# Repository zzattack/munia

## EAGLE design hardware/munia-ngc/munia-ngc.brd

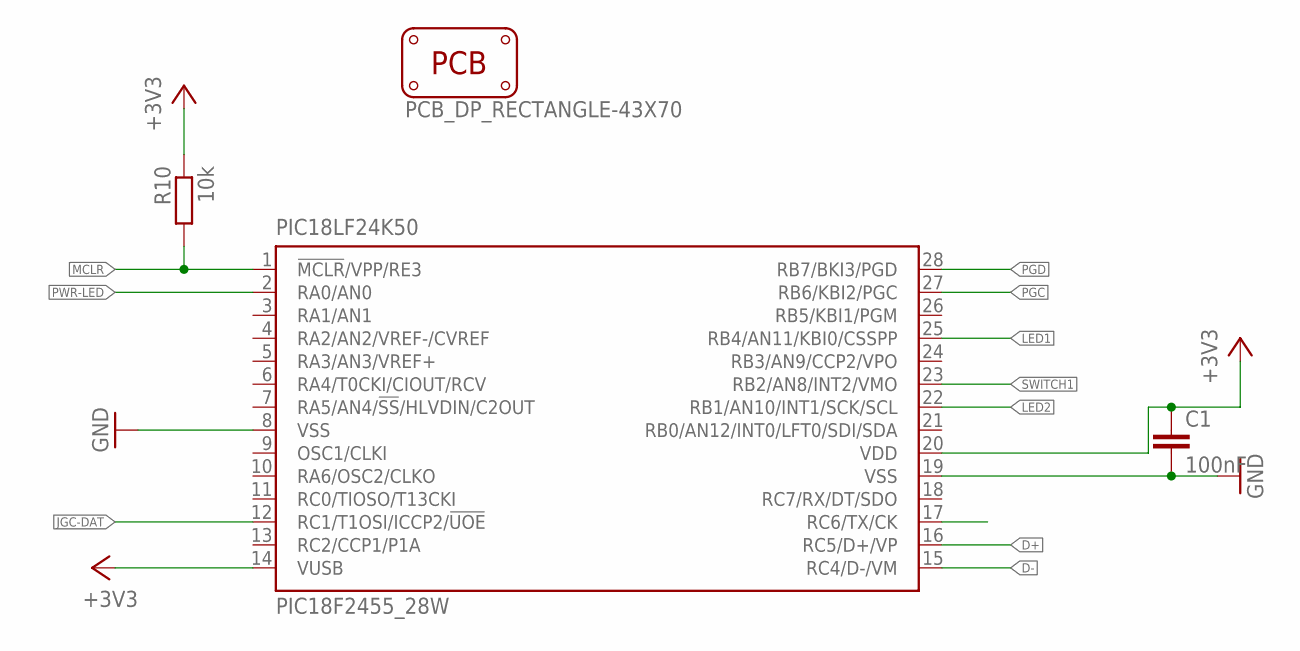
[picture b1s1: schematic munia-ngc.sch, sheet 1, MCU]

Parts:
C1: 100nF; C0603
PCB1: PCB_DP_RECTANGLE-43X70; DP7043_V1
PIC18LF24K50: PIC18F2455_28W; SO28W
R10: 10k; R0603

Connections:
+3V3: C1.1, PIC18LF24K50.14 (VUSB), PIC18LF24K50.20 (VDD), R10.1; also elsewhere on the board
D+: PIC18LF24K50.16 (RC5/D+/VP); also elsewhere on the board
D-: PIC18LF24K50.15 (RC4/D-/VM); also elsewhere on the board
GND: C1.2, PIC18LF24K50.8 (VSS), PIC18LF24K50.19 (VSS); also elsewhere on the board
JGC-DAT: PIC18LF24K50.12 (RC1/T1OSI/ICCP2/!UOE); also elsewhere on the board
LED1: PIC18LF24K50.25 (RB4/AN11/KBI0/CSSPP); also elsewhere on the board
LED2: PIC18LF24K50.22 (RB1/AN10/INT1/SCK/SCL); also elsewhere on the board
MCLR: PIC18LF24K50.1 (!MCLR!/VPP/RE3), R10.2; also elsewhere on the board
PGC: PIC18LF24K50.27 (RB6/KBI2/PGC); also elsewhere on the board
PGD: PIC18LF24K50.28 (RB7/BKI3/PGD); also elsewhere on the board
PWR-LED: PIC18LF24K50.2 (RA0/AN0); also elsewhere on the board
SWITCH1: PIC18LF24K50.23 (RB2/AN8/INT2/VMO); also elsewhere on the board

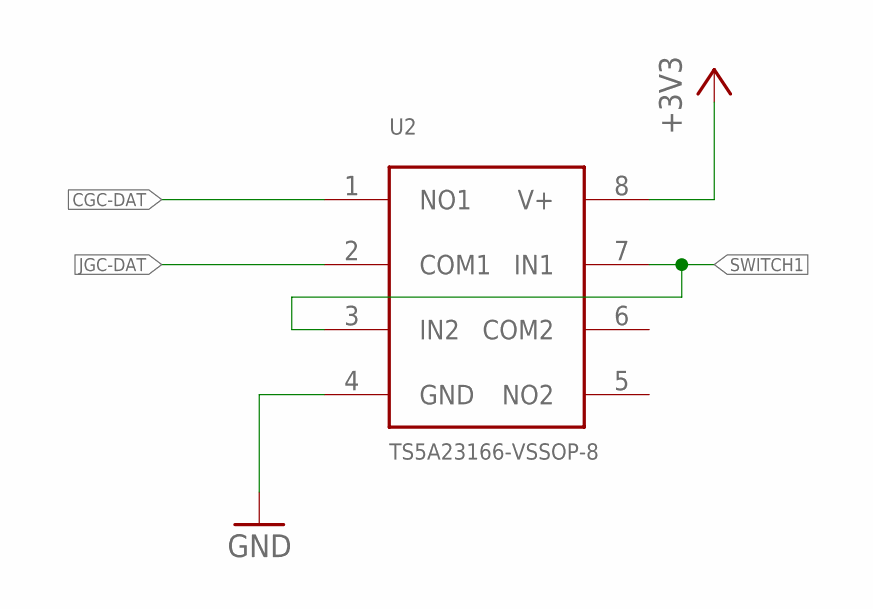
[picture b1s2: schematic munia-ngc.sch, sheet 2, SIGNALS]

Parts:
U2: TS5A23166-VSSOP-8; SOT765

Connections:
+3V3: U2.8 (V+); also elsewhere on the board
CGC-DAT: U2.1 (NO1); also elsewhere on the board
GND: U2.4 (GND); also elsewhere on the board
JGC-DAT: U2.2 (COM1); also elsewhere on the board
SWITCH1: U2.3 (IN2), U2.7 (IN1); also elsewhere on the board

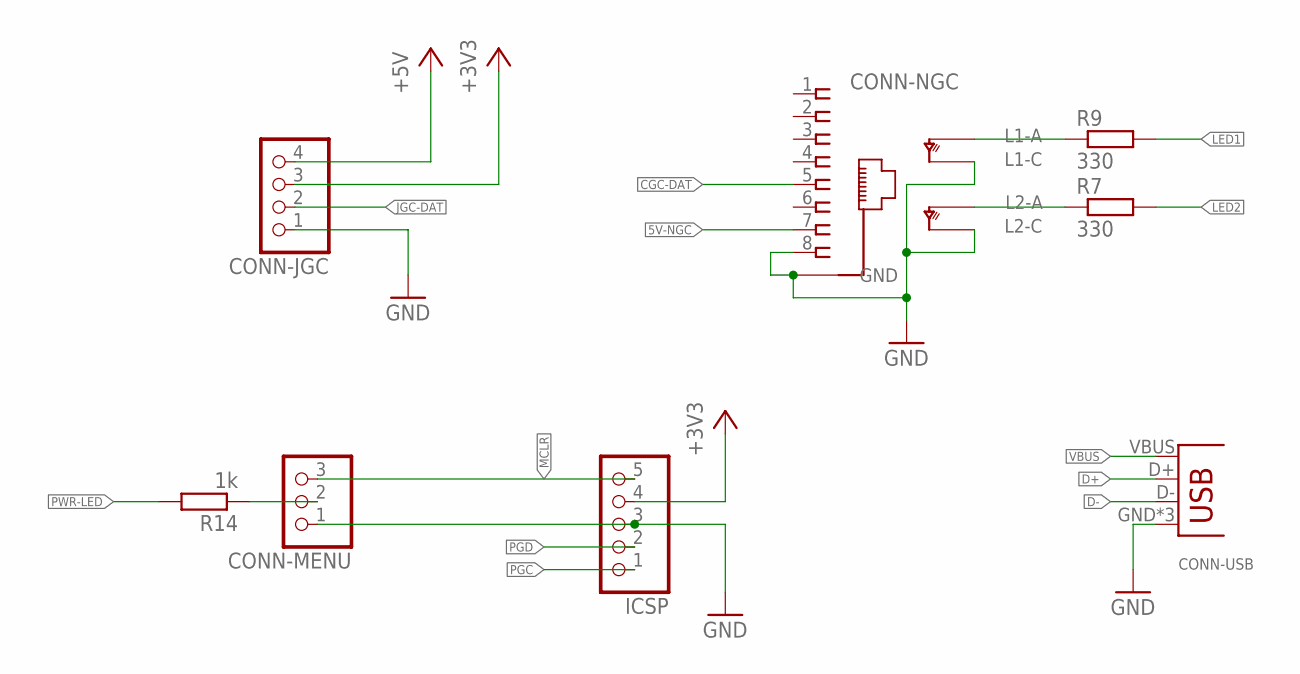
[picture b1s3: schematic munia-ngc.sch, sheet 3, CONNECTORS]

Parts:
CONN-JGC: PINHD-1X4; 1X04
CONN-MENU: PINHD-1X3; 1X03
CONN-NGC: RJ45-NIELS
CONN-USB: USB-B-NIELS; USB-B-H
ICSP: PINHD-1X5; 1X05
R7, R9: 330; R0603
R14: 1k; R0603

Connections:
5V-NGC: CONN-NGC.7; also elsewhere on the board
+3V3: CONN-JGC.3, ICSP.4; also elsewhere on the board
+5V: CONN-JGC.4; also elsewhere on the board
CGC-DAT: CONN-NGC.5; also elsewhere on the board
D+: CONN-USB.D+; also elsewhere on the board
D-: CONN-USB.D-; also elsewhere on the board
GND: CONN-JGC.1, CONN-MENU.1, CONN-NGC.8, CONN-NGC.GND@5 (GND), CONN-NGC.GND@6 (GND), CONN-NGC.LED-GREEN-C (L2C), CONN-NGC.LED-ORANGE-C (L1C), CONN-USB.GND, CONN-USB.GND@1 (GND), CONN-USB.GND@2 (GND), ICSP.3; also elsewhere on the board
JGC-DAT: CONN-JGC.2; also elsewhere on the board
LED1: R9.2; also elsewhere on the board
LED2: R7.2; also elsewhere on the board
MCLR: CONN-MENU.3, ICSP.5; also elsewhere on the board
unnamed: CONN-MENU.2, R14.1
unnamed: CONN-NGC.LED-ORANGE-A (L1A), R9.1
unnamed: CONN-NGC.LED-GREEN-A (L2A), R7.1
PGC: ICSP.1; also elsewhere on the board
PGD: ICSP.2; also elsewhere on the board
PWR-LED: R14.2; also elsewhere on the board
VBUS: CONN-USB.VBUS; also elsewhere on the board

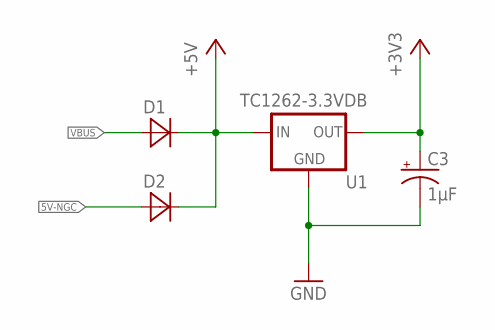
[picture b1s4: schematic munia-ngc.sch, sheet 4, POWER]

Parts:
C3: 1µF; EIA3216
D1, D2: MBR120VLSFT1G; SOD123
U1: TC1262-3.3VDB; SOT230P700X180-4N

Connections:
5V-NGC: D2.2 (A); also elsewhere on the board
+3V3: C3.A (+), U1.3 (OUT); also elsewhere on the board
+5V: D1.1 (C), D2.1 (C), U1.1 (IN); also elsewhere on the board
GND: C3.C (-), U1.2 (GND), U1.4 (GND); also elsewhere on the board
VBUS: D1.2 (A); also elsewhere on the board

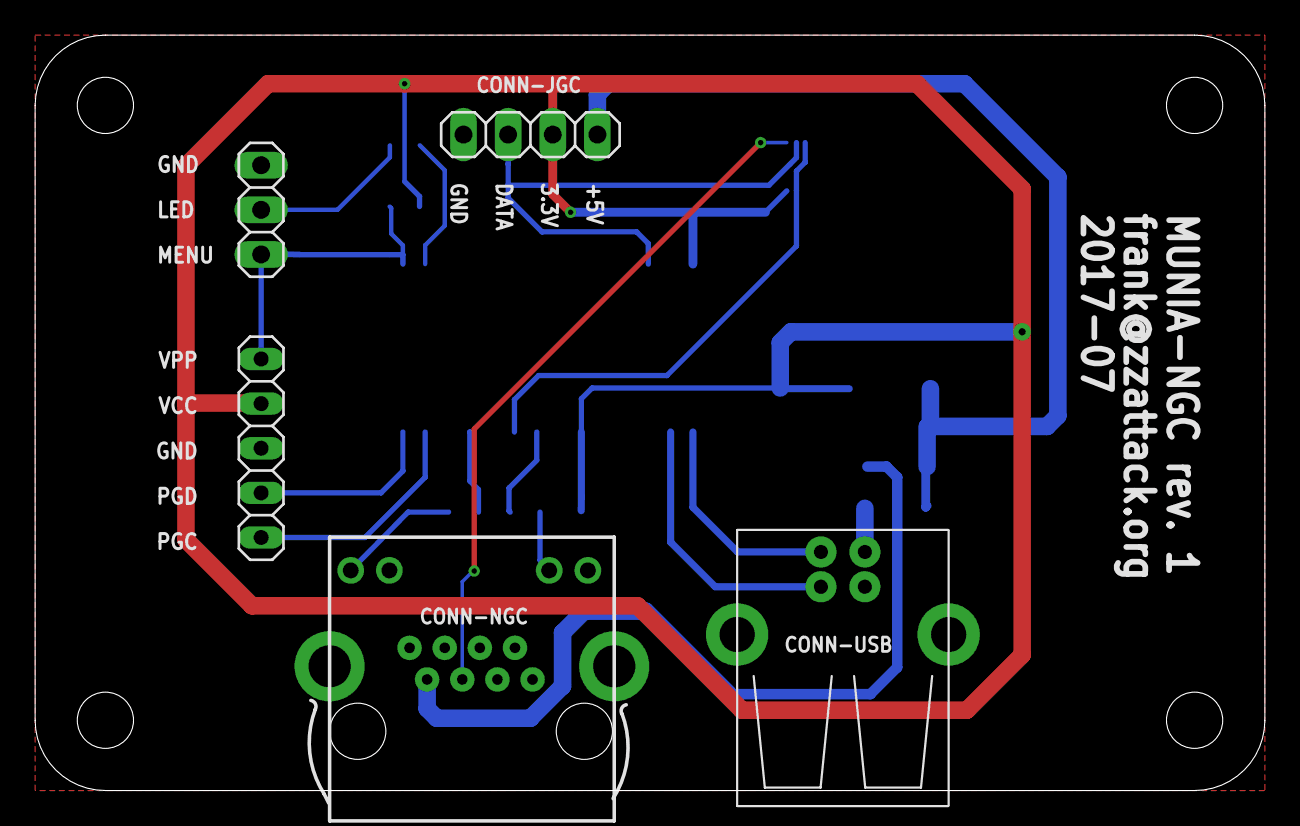
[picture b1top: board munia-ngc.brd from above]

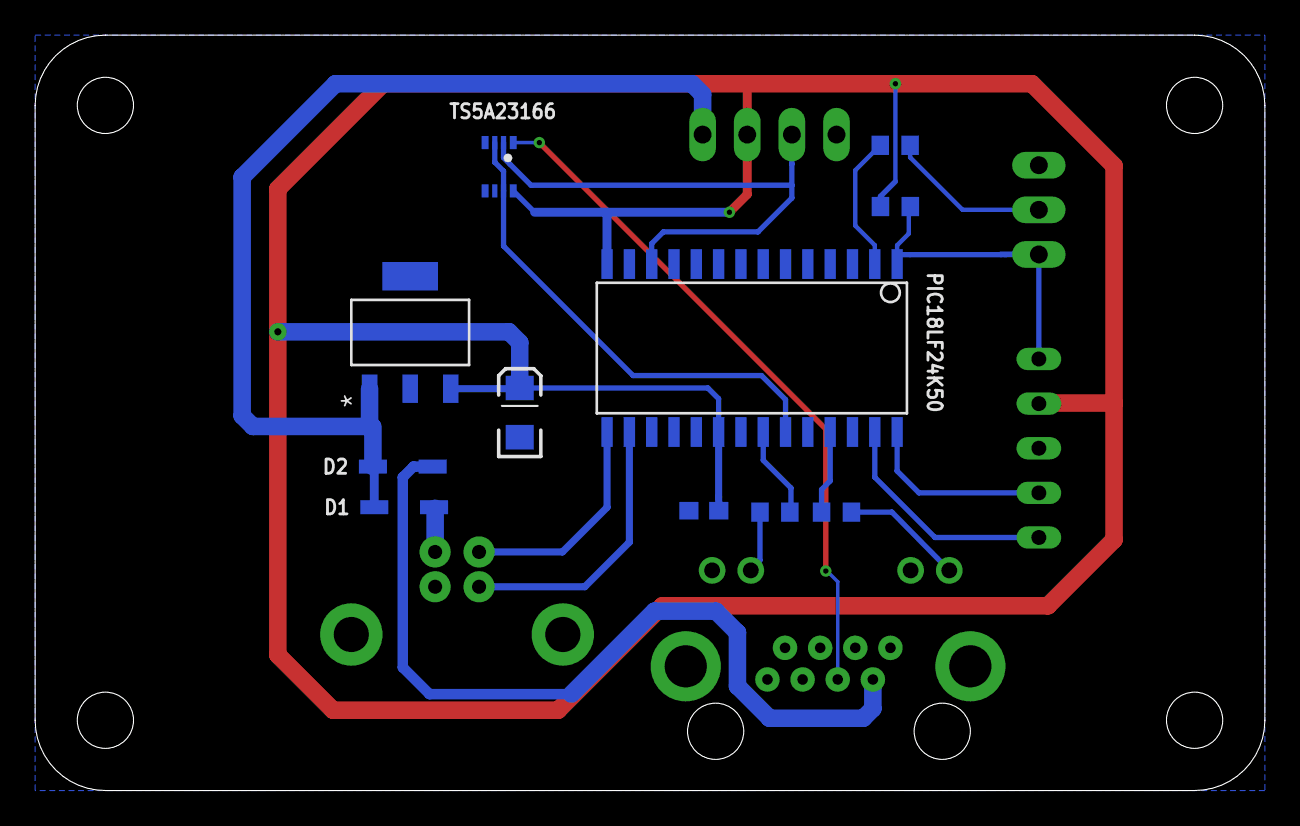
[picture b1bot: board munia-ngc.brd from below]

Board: 2 copper layers, 70.0 x 43.0 mm, 17 parts (11 on the bottom side), 19 nets.

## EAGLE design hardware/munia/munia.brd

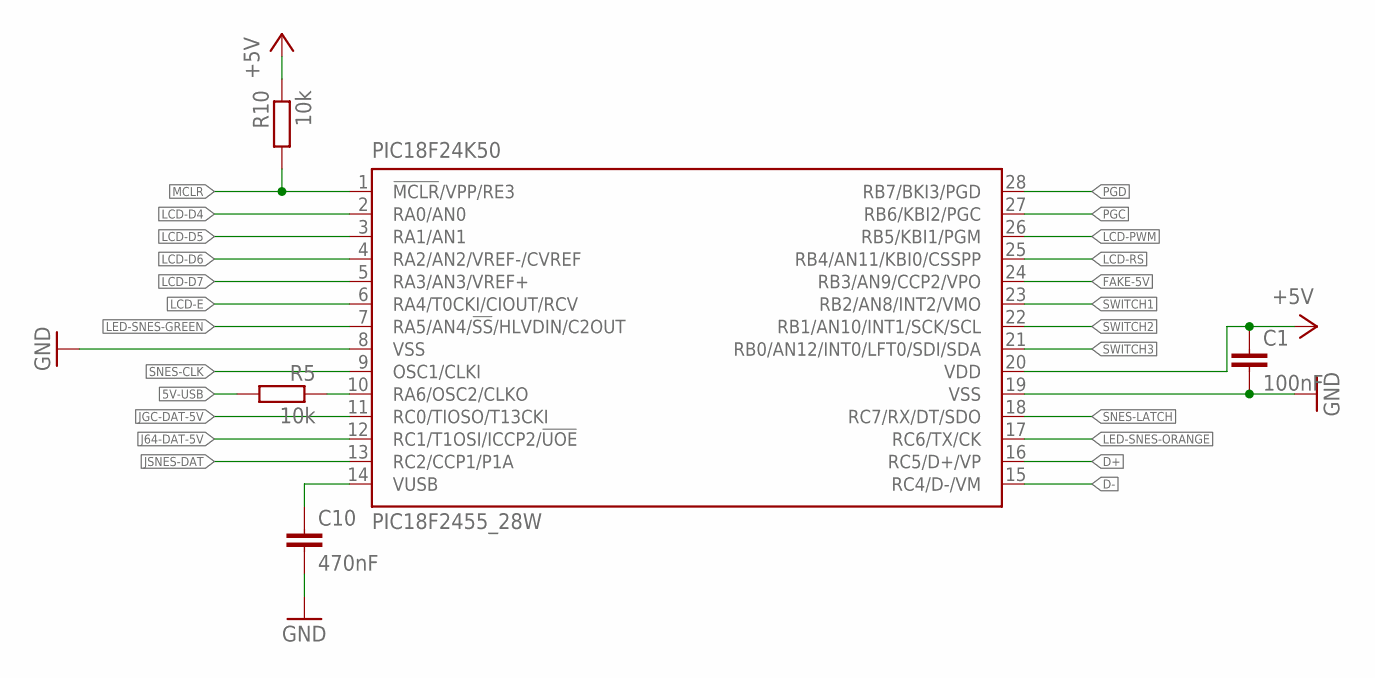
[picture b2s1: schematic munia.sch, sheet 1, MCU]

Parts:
C1: 100nF; C0603
C10: 470nF; C0603
PIC18F24K50: PIC18F2455_28W; SO28W
R5, R10: 10k; R0603

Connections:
5V-USB: R5.2; also elsewhere on the board
+5V: C1.1, PIC18F24K50.20 (VDD), R10.1; also elsewhere on the board
D+: PIC18F24K50.16 (RC5/D+/VP); also elsewhere on the board
D-: PIC18F24K50.15 (RC4/D-/VM); also elsewhere on the board
FAKE-5V: PIC18F24K50.24 (RB3/AN9/CCP2/VPO); also elsewhere on the board
J64-DAT-5V: PIC18F24K50.12 (RC1/T1OSI/ICCP2/!UOE); also elsewhere on the board
JGC-DAT-5V: PIC18F24K50.11 (RC0/TIOSO/T13CKI); also elsewhere on the board
JSNES-DAT: PIC18F24K50.13 (RC2/CCP1/P1A); also elsewhere on the board
LCD-D4: PIC18F24K50.2 (RA0/AN0); also elsewhere on the board
LCD-D5: PIC18F24K50.3 (RA1/AN1); also elsewhere on the board
LCD-D6: PIC18F24K50.4 (RA2/AN2/VREF-/CVREF); also elsewhere on the board
LCD-D7: PIC18F24K50.5 (RA3/AN3/VREF+); also elsewhere on the board
LCD-E: PIC18F24K50.6 (RA4/T0CKI/CIOUT/RCV); also elsewhere on the board
LCD-PWM: PIC18F24K50.26 (RB5/KBI1/PGM); also elsewhere on the board
LCD-RS: PIC18F24K50.25 (RB4/AN11/KBI0/CSSPP); also elsewhere on the board
LED-SNES-GREEN: PIC18F24K50.7 (RA5/AN4/!SS!/HLVDIN/C2OUT); also elsewhere on the board
LED-SNES-ORANGE: PIC18F24K50.17 (RC6/TX/CK); also elsewhere on the board
MCLR: PIC18F24K50.1 (!MCLR!/VPP/RE3), R10.2; also elsewhere on the board
unnamed: C10.1, PIC18F24K50.14 (VUSB)
SNES-CLK: PIC18F24K50.9 (OSC1/CLKI); also elsewhere on the board
SNES-LATCH: PIC18F24K50.18 (RC7/RX/DT/SDO); also elsewhere on the board
SWITCH1: PIC18F24K50.23 (RB2/AN8/INT2/VMO); also elsewhere on the board
SWITCH2: PIC18F24K50.22 (RB1/AN10/INT1/SCK/SCL); also elsewhere on the board
SWITCH3: PIC18F24K50.21 (RB0/AN12/INT0/LFT0/SDI/SDA); also elsewhere on the board
USB-SENSE: PIC18F24K50.10 (RA6/OSC2/CLKO), R5.1

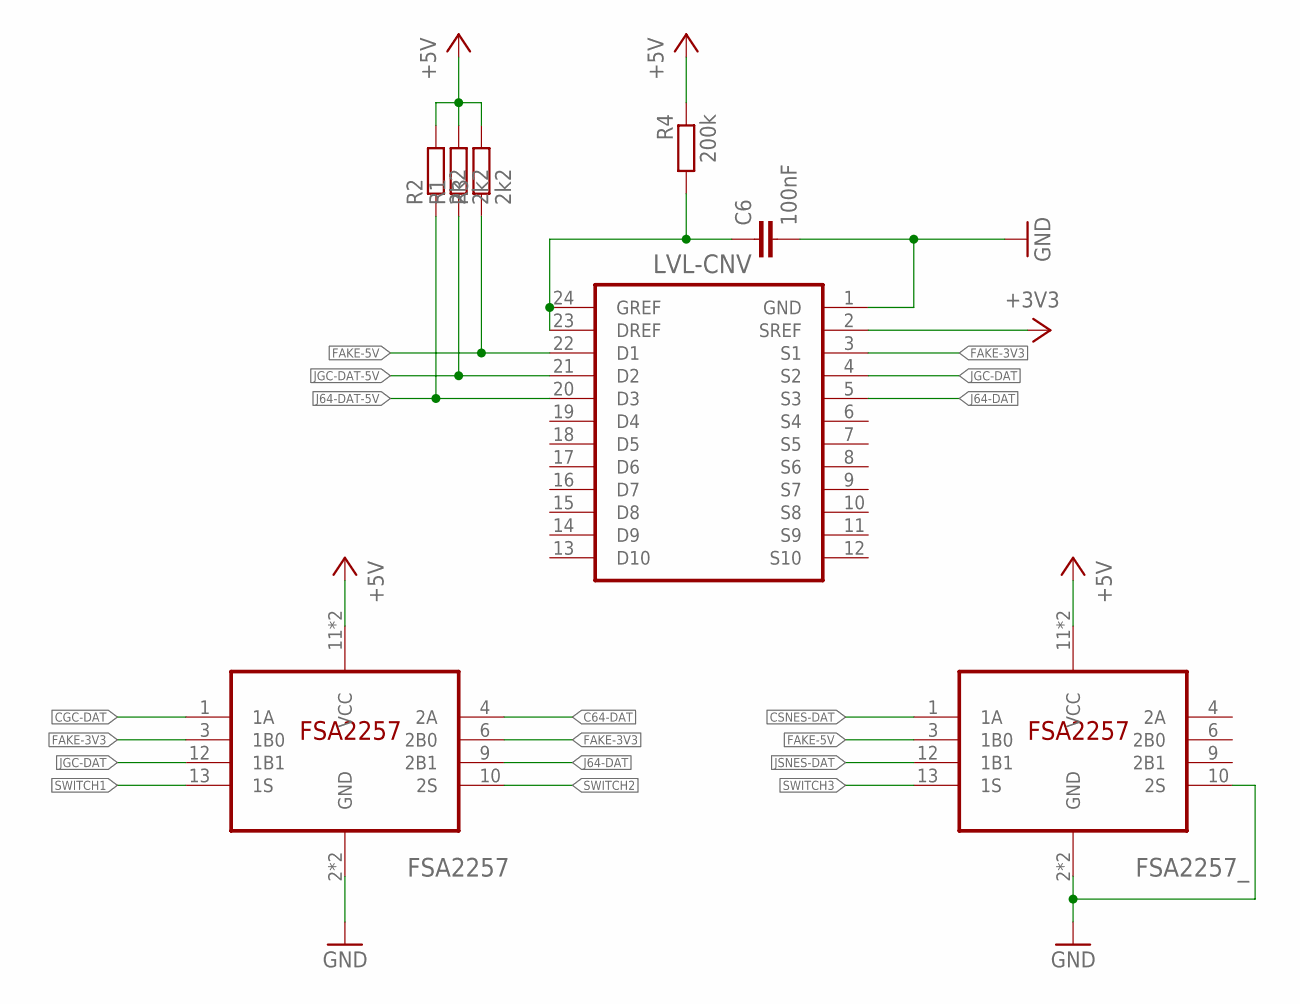
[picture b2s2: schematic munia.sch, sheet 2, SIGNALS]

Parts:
C6: 100nF; C0603
FSA2257, FSA2257_: FSA2257MTCX; TSSOP14
LVL-CNV: GTL2010; TSSOP24
R1, R2, R3: 2k2; R0603
R4: 200k; R0603

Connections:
+3V3: LVL-CNV.2 (SREF); also elsewhere on the board
+5V: FSA2257.11 (VCC), FSA2257.14 (VCC), FSA2257_.11 (VCC), FSA2257_.14 (VCC), R1.2, R2.2, R3.2, R4.1; also elsewhere on the board
C64-DAT: FSA2257.4 (2A); also elsewhere on the board
CGC-DAT: FSA2257.1 (1A); also elsewhere on the board
CSNES-DAT: FSA2257_.1 (1A); also elsewhere on the board
FAKE-3V3: FSA2257.3 (1B0), FSA2257.6 (2B0), LVL-CNV.3 (S1)
FAKE-5V: FSA2257_.3 (1B0), LVL-CNV.22 (D1), R3.1; also elsewhere on the board
J64-DAT: FSA2257.9 (2B1), LVL-CNV.5 (S3); also elsewhere on the board
J64-DAT-5V: LVL-CNV.20 (D3), R2.1; also elsewhere on the board
JGC-DAT: FSA2257.12 (1B1), LVL-CNV.4 (S2); also elsewhere on the board
JGC-DAT-5V: LVL-CNV.21 (D2), R1.1; also elsewhere on the board
JSNES-DAT: FSA2257_.12 (1B1); also elsewhere on the board
unnamed: C6.1, LVL-CNV.23 (DREF), LVL-CNV.24 (GREF), R4.2
SWITCH1: FSA2257.13 (1S); also elsewhere on the board
SWITCH2: FSA2257.10 (2S); also elsewhere on the board
SWITCH3: FSA2257_.13 (1S); also elsewhere on the board

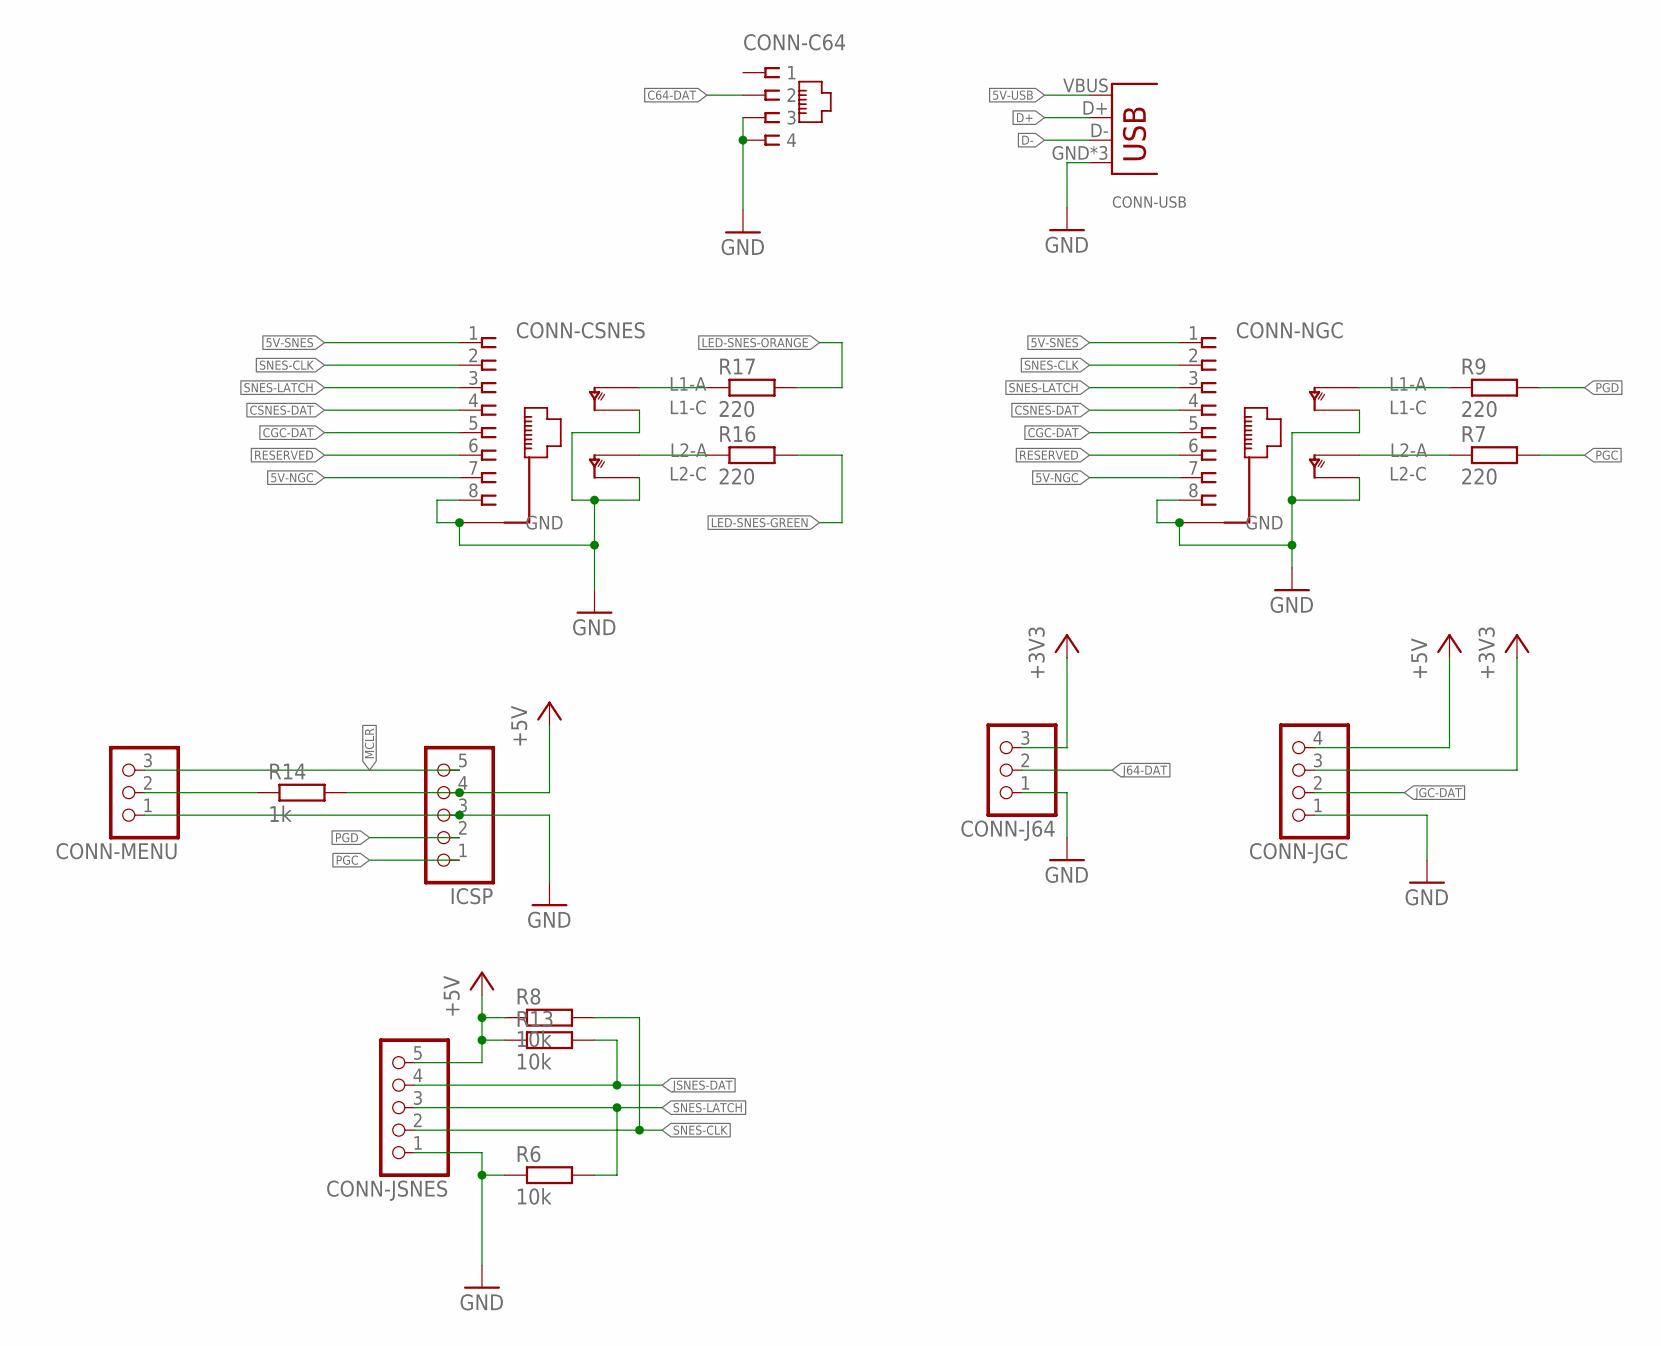
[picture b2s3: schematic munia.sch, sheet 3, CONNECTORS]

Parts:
CONN-C64: RJ11-6P4C; RJ11-4C
CONN-CSNES: RJ45-NIELS
CONN-J64: PINHD-1X3; 1X03
CONN-JGC: PINHD-1X4; 1X04
CONN-JSNES: PINHD-1X5; 1X05
CONN-MENU: PINHD-1X3; 1X03
CONN-NGC: RJ45-NIELS
CONN-USB: USB-B-NIELS; USB-B-H
ICSP: PINHD-1X5; 1X05
R6, R8, R13: 10k; R0603
R7, R9, R16, R17: 220; R0603
R14: 1k; R0603

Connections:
5V-NGC: CONN-CSNES.7, CONN-NGC.7; also elsewhere on the board
5V-SNES: CONN-CSNES.1, CONN-NGC.1; also elsewhere on the board
5V-USB: CONN-USB.VBUS; also elsewhere on the board
+3V3: CONN-J64.3, CONN-JGC.3; also elsewhere on the board
+5V: CONN-C64.5, CONN-JGC.4, CONN-JSNES.5, ICSP.4, R8.1, R13.1, R14.2; also elsewhere on the board
C64-DAT: CONN-C64.1; also elsewhere on the board
CGC-DAT: CONN-CSNES.5, CONN-NGC.5; also elsewhere on the board
CSNES-DAT: CONN-CSNES.4, CONN-NGC.4; also elsewhere on the board
D+: CONN-USB.D+; also elsewhere on the board
D-: CONN-USB.D-; also elsewhere on the board
J64-DAT: CONN-J64.2; also elsewhere on the board
JGC-DAT: CONN-JGC.2; also elsewhere on the board
JSNES-DAT: CONN-JSNES.4, R13.2; also elsewhere on the board
LED-SNES-GREEN: R16.2; also elsewhere on the board
LED-SNES-ORANGE: R17.2; also elsewhere on the board
MCLR: CONN-C64.6, CONN-MENU.3, ICSP.5; also elsewhere on the board
unnamed: CONN-CSNES.LED-ORANGE-A (L1A), R17.1
unnamed: CONN-CSNES.LED-GREEN-A (L2A), R16.1
unnamed: CONN-NGC.LED-ORANGE-A (L1A), R9.1
unnamed: CONN-NGC.LED-GREEN-A (L2A), R7.1
PWR-LED: CONN-MENU.2, R14.1
RESERVED: CONN-CSNES.6, CONN-NGC.6
SNES-CLK: CONN-CSNES.2, CONN-JSNES.2, CONN-NGC.2, R8.2; also elsewhere on the board
SNES-LATCH: CONN-CSNES.3, CONN-JSNES.3, CONN-NGC.3, R6.2; also elsewhere on the board

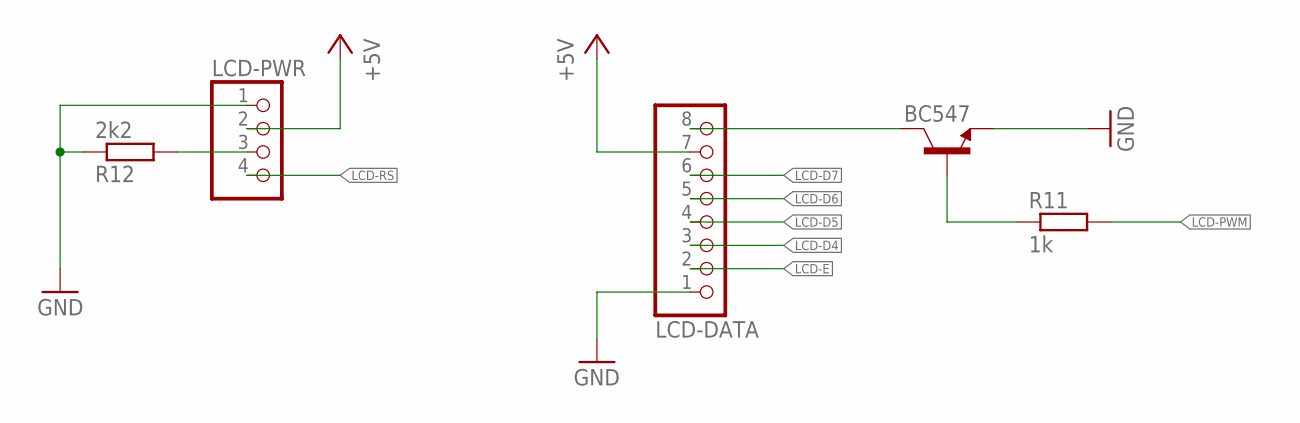
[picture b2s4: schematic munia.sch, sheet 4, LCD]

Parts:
BC547: BC847; SOT23
LCD-DATA: PINHD-1X8; 1X08
LCD-PWR: PINHD-1X4; 1X04
R11: 1k; R0603
R12: 2k2; R0603

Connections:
+5V: LCD-DATA.7, LCD-PWR.2; also elsewhere on the board
C: BC547.3 (C), LCD-DATA.8
LCD-D4: LCD-DATA.3; also elsewhere on the board
LCD-D5: LCD-DATA.4; also elsewhere on the board
LCD-D6: LCD-DATA.5; also elsewhere on the board
LCD-D7: LCD-DATA.6; also elsewhere on the board
LCD-E: LCD-DATA.2; also elsewhere on the board
LCD-PWM: R11.2; also elsewhere on the board
LCD-RS: LCD-PWR.4; also elsewhere on the board
unnamed: BC547.1 (B), R11.1
VEE: LCD-PWR.3, R12.2

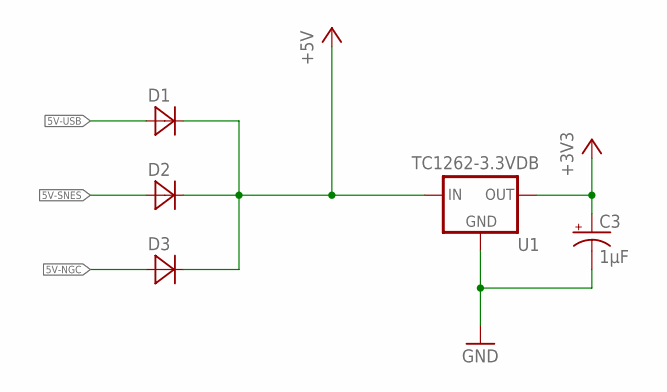
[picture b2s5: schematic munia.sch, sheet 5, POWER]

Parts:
C3: 1µF; EIA3216
D1, D2, D3: MBR120VLSFT1G; SOD123
U1: TC1262-3.3VDB; SOT230P700X180-4N

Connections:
5V-NGC: D3.2 (A); also elsewhere on the board
5V-SNES: D2.2 (A); also elsewhere on the board
5V-USB: D1.2 (A); also elsewhere on the board
+3V3: C3.A (+), U1.3 (OUT); also elsewhere on the board
+5V: D1.1 (C), D2.1 (C), D3.1 (C), U1.1 (IN); also elsewhere on the board

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
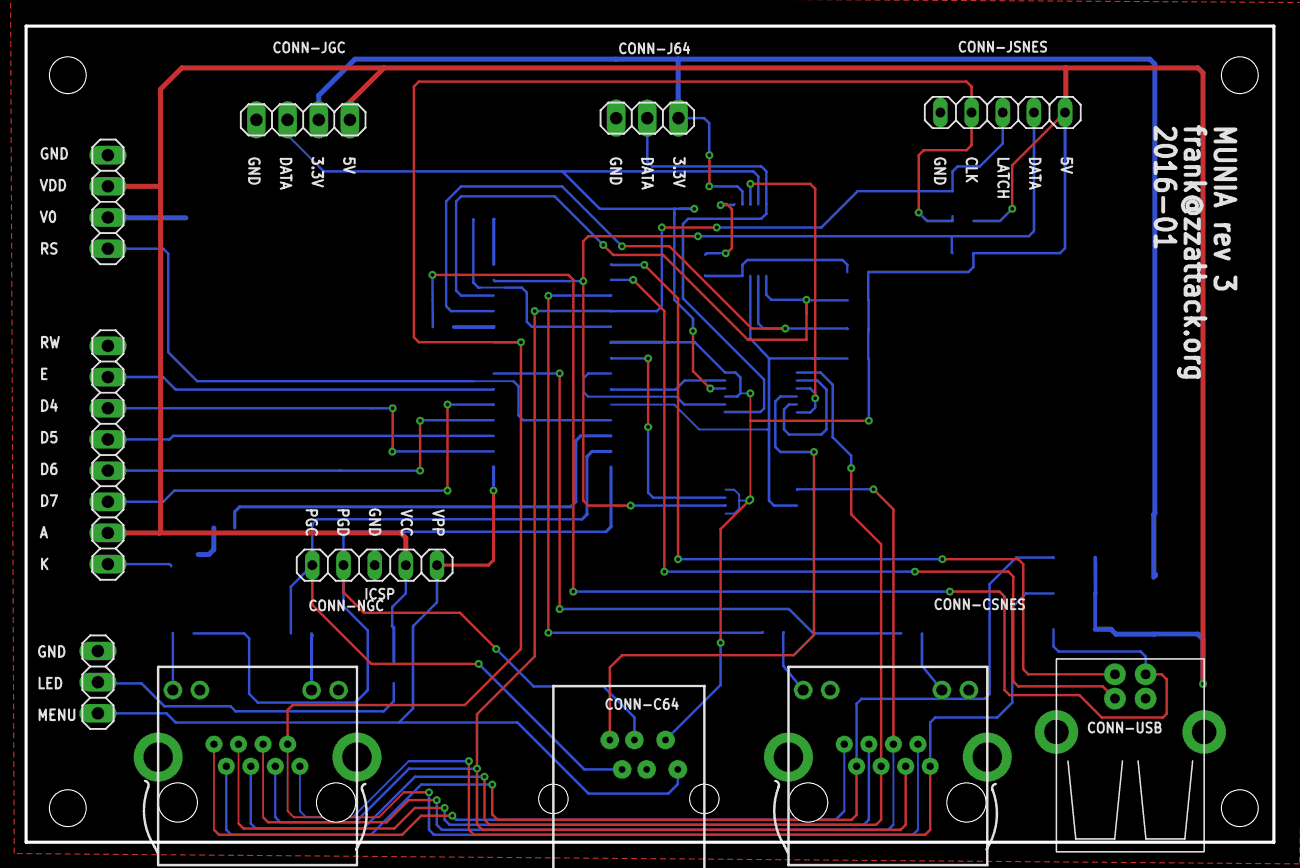
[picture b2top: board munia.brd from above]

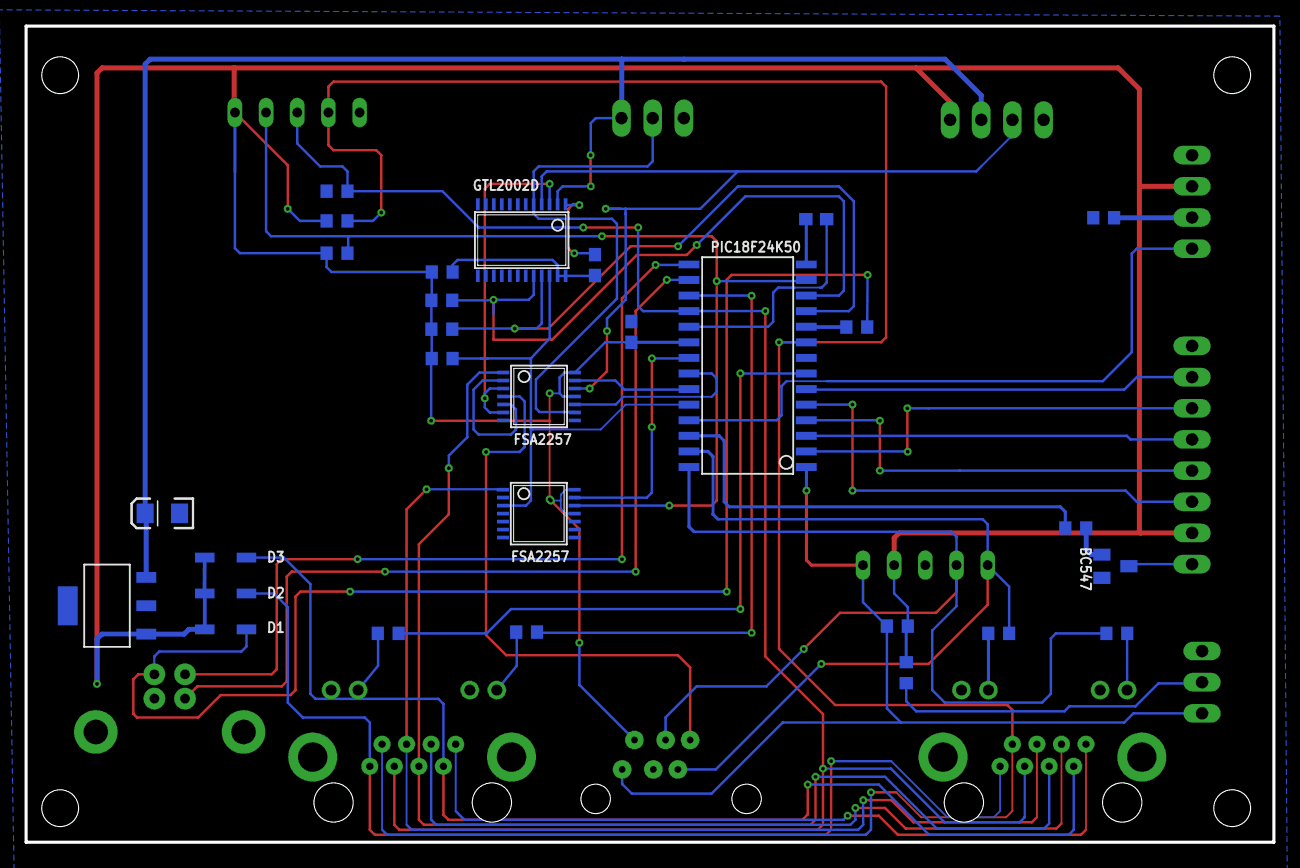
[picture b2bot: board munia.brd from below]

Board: 2 copper layers, 101.7 x 66.5 mm, 40 parts (29 on the bottom side), 47 nets.

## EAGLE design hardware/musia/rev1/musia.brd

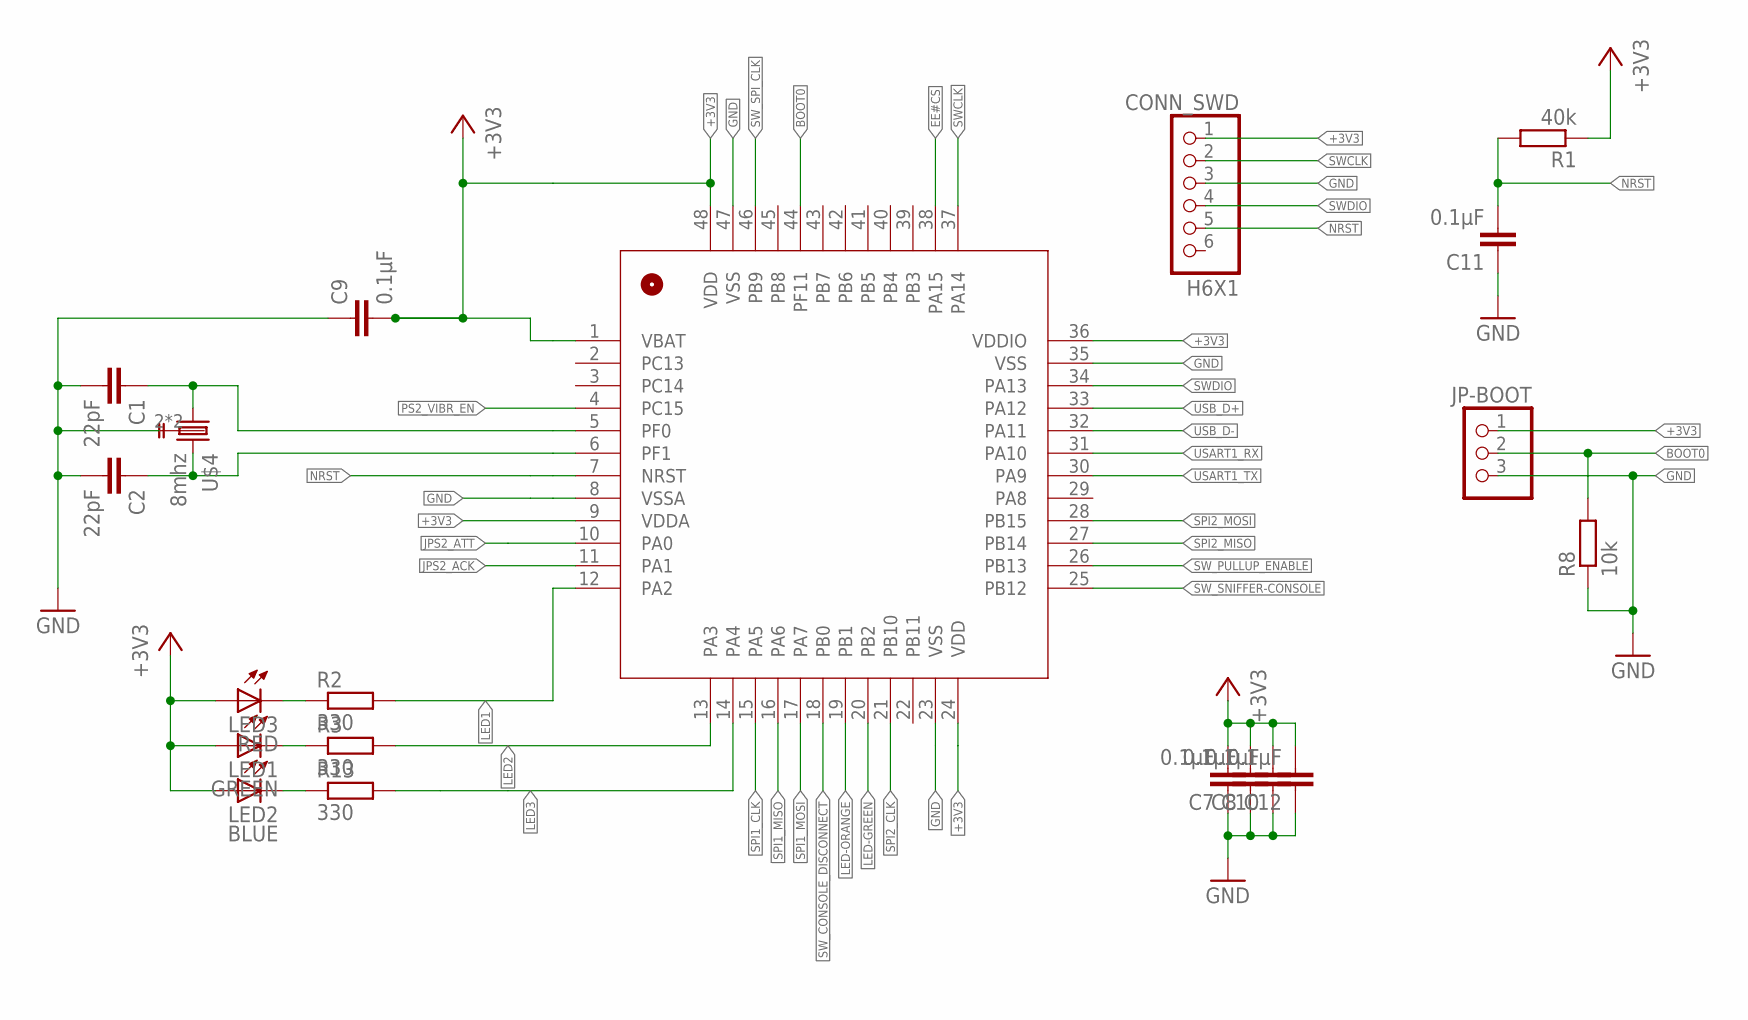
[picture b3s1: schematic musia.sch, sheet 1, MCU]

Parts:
C1, C2: 22pF; C0603
C7, C8, C9, C10, C11, C12: 0.1µF; C0603
CONN_SWD: H6X1; 1X06
JP-BOOT: PINHD-1X3; 1X03
LED1: GREEN; CHIPLED_0805
LED2: BLUE; CHIPLED_0805
LED3: RED; CHIPLED_0805
R1: 40k; R0603
R2, R3, R13: 330; R0603
R8: 10k; R0603
U$1: STM32F042; LQFP48-7X7
U$4: 8mhz; ABM3B

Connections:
+3V3: C7.2, C8.2, C9.2, C10.2, C12.2, CONN_SWD.1, JP-BOOT.1, LED1.A, LED2.A, LED3.A, R1.1, U$1.1 (VBAT), U$1.9 (VDDA), U$1.24 (VDD), U$1.36 (VDDIO), U$1.48 (VDD); also elsewhere on the board
BOOT0: JP-BOOT.2, R8.2, U$1.44 (PF11)
EE#CS: U$1.38 (PA15); also elsewhere on the board
GND: C1.2, C2.2, C7.1, C8.1, C9.1, C10.1, C11.1, C12.1, CONN_SWD.3, JP-BOOT.3, R8.1, U$1.8 (VSSA), U$1.23 (VSS), U$1.35 (VSS), U$1.47 (VSS), U$4.2 (GND), U$4.4 (GND); also elsewhere on the board
JPS2_ACK: U$1.11 (PA1); also elsewhere on the board
JPS2_ATT: U$1.10 (PA0); also elsewhere on the board
LED1: R2.2, U$1.12 (PA2)
LED2: R3.2, U$1.13 (PA3)
LED3: R13.2, U$1.14 (PA4)
LED-GREEN: U$1.20 (PB2); also elsewhere on the board
LED-ORANGE: U$1.19 (PB1); also elsewhere on the board
unnamed: LED3.C, R2.1
unnamed: LED2.C, R13.1
unnamed: LED1.C, R3.1
unnamed: C2.1, U$1.6 (PF1), U$4.3 (2)
unnamed: C1.1, U$1.5 (PF0), U$4.1
NRST: C11.2, CONN_SWD.5, R1.2, U$1.7 (NRST)
PS2_VIBR_EN: U$1.4 (PC15); also elsewhere on the board
SPI1_CLK: U$1.15 (PA5); also elsewhere on the board
SPI1_MISO: U$1.16 (PA6); also elsewhere on the board
SPI1_MOSI: U$1.17 (PA7); also elsewhere on the board
SPI2_CLK: U$1.21 (PB10); also elsewhere on the board
SPI2_MISO: U$1.27 (PB14); also elsewhere on the board
SPI2_MOSI: U$1.28 (PB15); also elsewhere on the board
SWCLK: CONN_SWD.2, U$1.37 (PA14)
SWDIO: CONN_SWD.4, U$1.34 (PA13)
SW_CONSOLE_DISCONNECT: U$1.18 (PB0); also elsewhere on the board
SW_PULLUP_ENABLE: U$1.26 (PB13); also elsewhere on the board
SW_SNIFFER-CONSOLE: U$1.25 (PB12); also elsewhere on the board
SW_SPI_CLK: U$1.46 (PB9); also elsewhere on the board
USART1_RX: U$1.31 (PA10); also elsewhere on the board
USART1_TX: U$1.30 (PA9); also elsewhere on the board
USB_D+: U$1.33 (PA12); also elsewhere on the board
USB_D-: U$1.32 (PA11); also elsewhere on the board
